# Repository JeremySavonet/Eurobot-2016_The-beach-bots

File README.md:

EUROBOT 2016 - The Beach Bots
====

TODO <br><br>

<h4>HW description:</h4>
----

Board : https://www.olimex.com/Products/ARM/ST/STM32-E407/open-source-hardware <br>
Motor Driver : https://www.olimex.com/Products/RobotParts/MotorDrivers/BB-VNH3SP30/open-source-hardware<br>
WiFi IoT module : https://www.olimex.com/Products/IoT/MOD-WIFI-ESP8266/open-source-hardware<br> 
=> Github : https://github.com/espressif/esp8266_at<br>

<h4>SW description:</h4>
----

Need to test those two RTOS:<br>

<li>Freertos : https://github.com/frtos-wpan/freertos-201309/tree/master/FreeRTOS/Demo/E407</li>
<li>ChibiOS : http://chibios.org/dokuwiki/doku.php?id=chibios:documentation:start</li>
    
Chibios seems to be a better alternative than FreeRtos for severals reasons:<br>
<li>maintaining our own hal eats a lot of development time - ChibiOS comes with a hal</li>
<li>pios hal is not being widely used and tested - ChibiOS is</li>
<li>FreeRTOS relies 100% on dynamic memory allocation (heap) - ChibiOS can do static as well as dynamic memory (even mixed)</li>
<li>FreeRTOS api is not type safe (mutex / semaphore / queue) - ChibiOS api is type safe</li>
<li>i have a feeling that ChibiOS is more efficient than FreeRTOS</li>
<li>using ChibiOS hal will make us stop relying on the buggy ST libraries in the longer term</li>

<h5>How to setup the env:</h5>

<li>Install arm gcc:</li>
<ul>brew tap PX4/homebrew-px4</ul>
<ul>brew update</ul>
<ul>brew install gcc-arm-none-eabi</ul>

<li>Install dfu-util:</li>
<ul>brew install dfu-util</ul>

<li>Make the projet:</li>
<ul>Just run make in the project folder</ul>

<li>Program the target:</li>
<ul>Put the device in dfu mode (set the jumper like explain in the manual</ul>
<ul>Run the command: dfu-util -v -d 0483:df11 -a 0 -s 0x08000000 -D prog.hex</ul>

<h4>Usefull links:</h4>
----

<li>https://www.alexwhittemore.com/using-the-stm32f4discovery-on-the-mac-os-x-10-8-4-command-line/</li>
<li>http://www.telecom-robotics.org/2013/08/robotics-101-quick-start/</li>

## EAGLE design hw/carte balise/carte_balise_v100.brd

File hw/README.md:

HW SECTION:
====

TODO:
----

<li> Add pull-up resistors </li>
<li> Update restrict zones </li>
<li> Update polygons clearance </li>

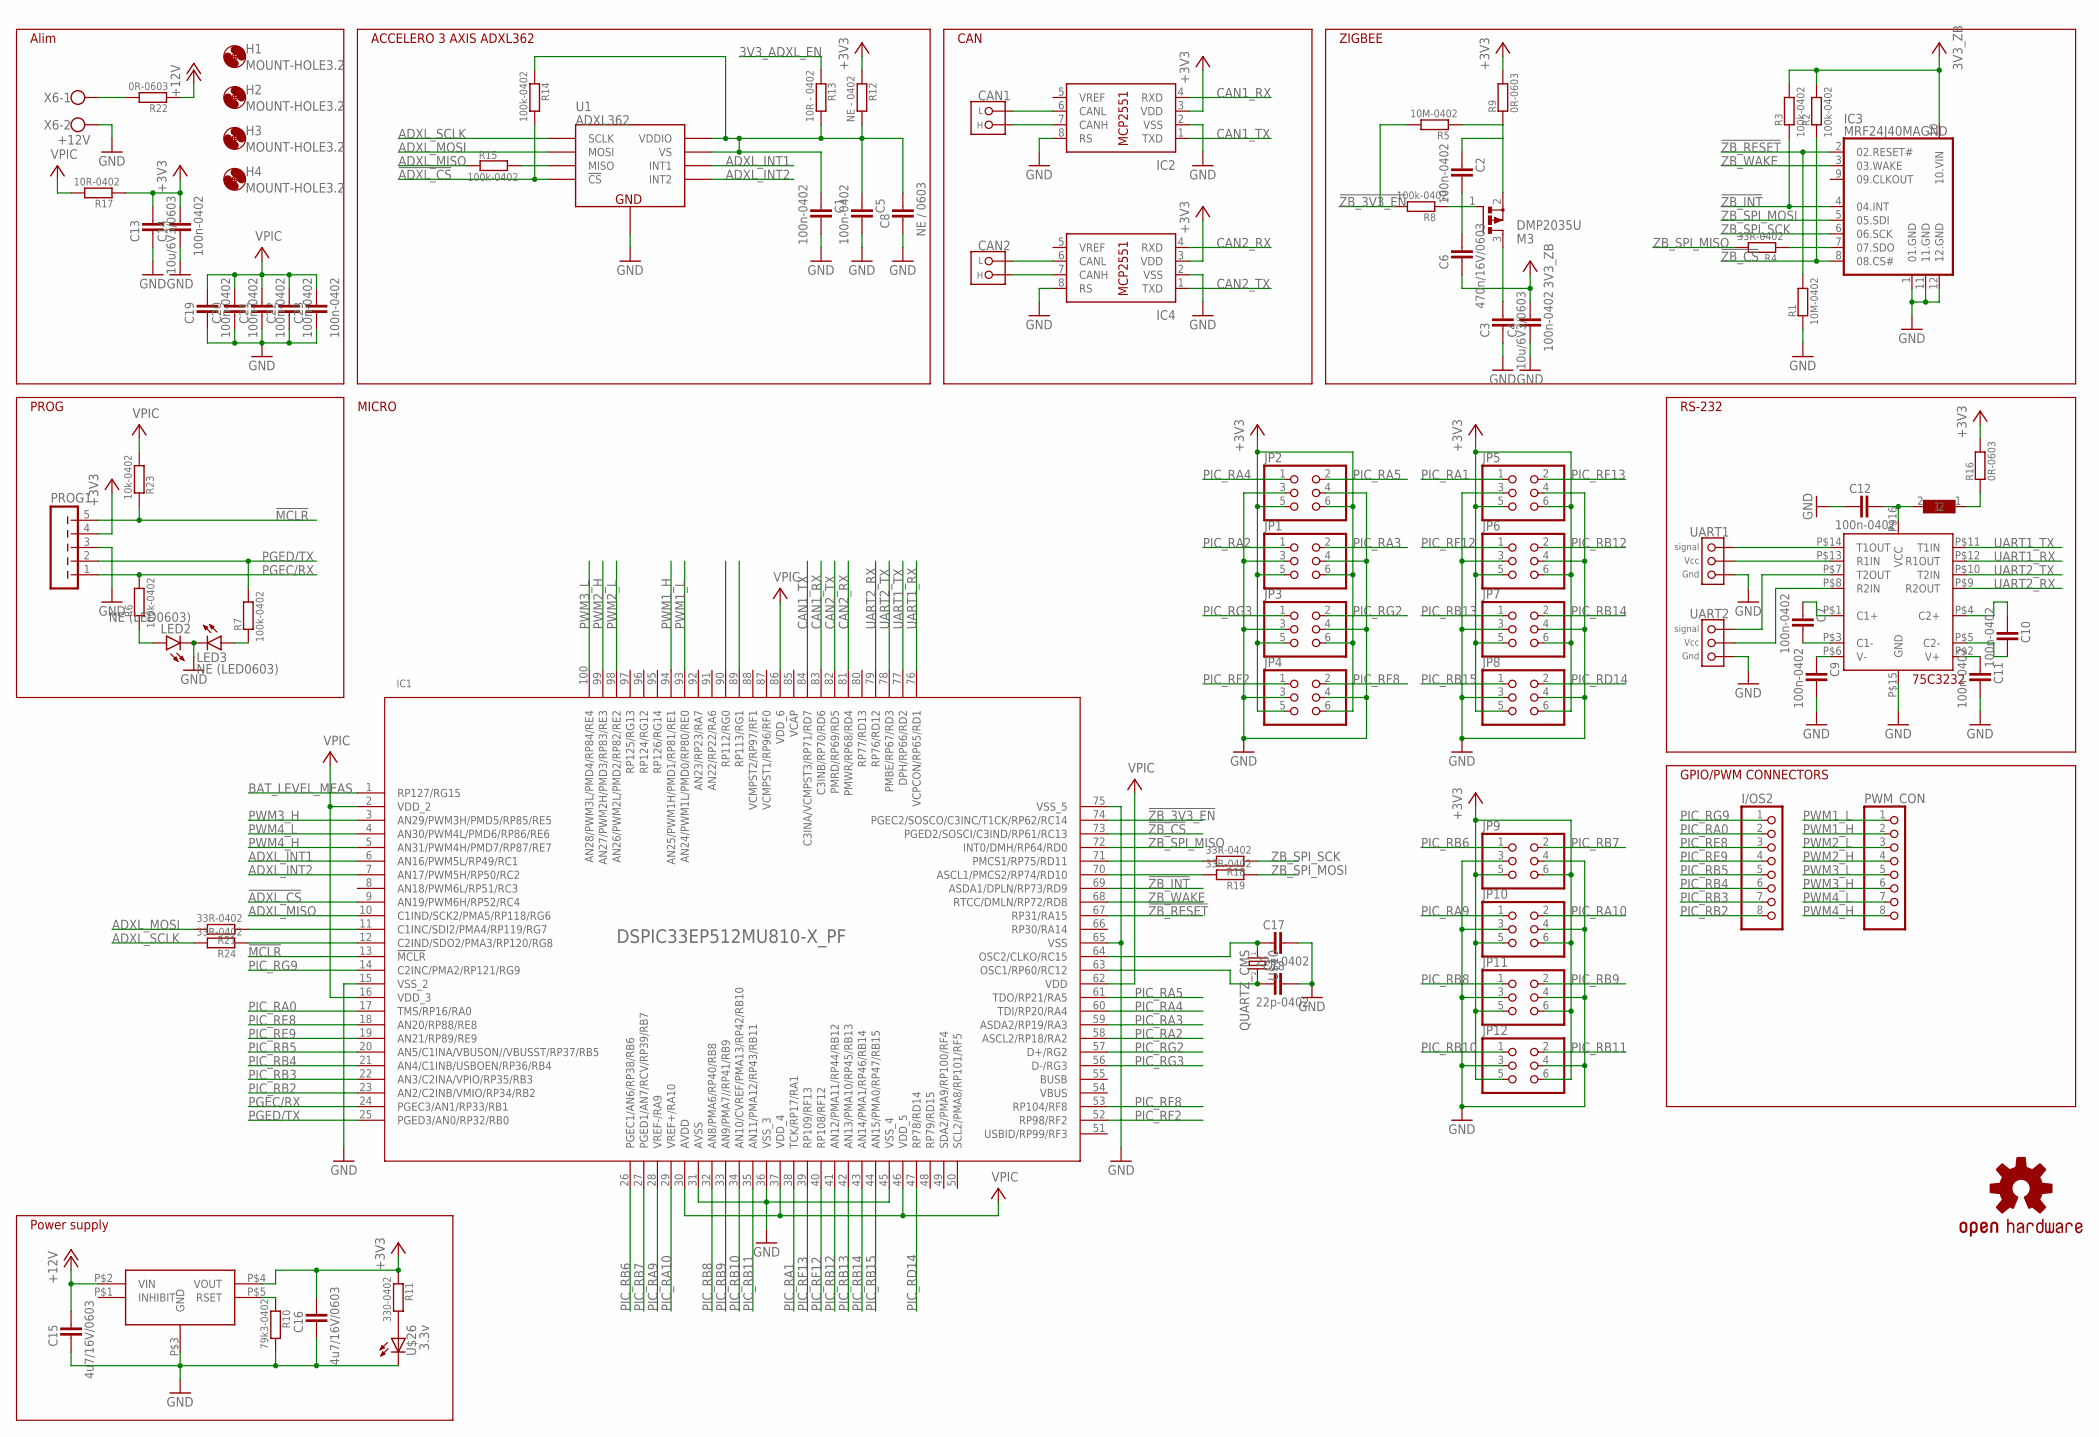
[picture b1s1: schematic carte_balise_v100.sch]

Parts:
C1, C2, C4, C5, C7, C9, C10, C11, C12, C14, C19, C20, C21, C22, C23: 100n-0402; 0402K
C3, C13: 10u/6V3/0603; 0603K
C6: 470n/16V/0603; 0603K
C8: NE / 0603; 0603K
C15, C16: 4u7/16V/0603; 0603K
C17, C18: 22p-0402; 0402K
CAN1, CAN2: CONNECT_CAN
H1, H2, H3, H4: MOUNT-HOLE3.2; 3,2
I/OS2: PINHD-1X08_2.54; 1X08
IC1: DSPIC33EP512MU810-X_PF; TQFP100_14X14MC
IC2, IC4: MCP2551/SN; SO08
IC3: MRF24J40MAGND; MRF24J40MA_2
JP1, JP2, JP3, JP4, JP5, JP6, JP7, JP8, JP9, JP10, JP11, JP12: PINHD-2X3; 2X03
LED2, LED3: NE (LED0603); 0603K
M3: DMP2035U; SOT23-3
PROG1: FE05-1
PWM_CON: PINHD-1X08_2.54; 1X08
R1, R5: 10M-0402; 0402K
R2, R3, R6, R7, R8, R14, R15: 100k-0402; 0402K
R4, R18, R19, R21, R24: 33R-0402; 0402K
R9, R16, R22: 0R-0603; 0603K
R10: 79k3-0402; 0402K
R11: 330-0402; 0402K
R12: NE - 0402; 0402K
R13: 10R - 0402; 0402K
R17: 10R-0402; 0402K
R23: 10k-0402; 0402K
U1: ADXL362
U$1: OSHW-LOGOS; OSHW-LOGO-S
U$2: SN75C3232_PW; PW16
U$3: L_603; 0603
U$10: QUARTZ_CMS
U$26: 3.3v; 805
U$27: PTR08100W
UART1, UART2: CONNECT_3PINS_CMS; CON_2.54_3
X6: +12V; W237-102

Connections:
3V3_ADXL_EN: R13.1
!ADXL_CS: IC1.9 (AN19/PWM6H/RP52/RC4), R14.2, U1.P$8 (!CS)
!MCLR: IC1.13 (!MCLR), PROG1.5, R23.1
!ZB_3V3_EN: IC1.74 (PGEC2/SOSCO/C3INC/T1CK/RP62/RC14), R5.2, R8.2
!ZB_CS: IC1.73 (PGED2/SOSCI/C3IND/RP61/RC13), IC3.8 (08.CS#), R2.1
!ZB_INT: IC1.69 (ASDA1/DPLN/RP73/RD9), IC3.4 (04.INT), R3.1
!ZB_RESET: IC1.67 (RP31/RA15), IC3.2 (02.RESET#), R1.2
+3V3: C13.1, C14.1, C16.1, IC2.3 (VDD), IC4.3 (VDD), JP1.5, JP1.6, JP2.5, JP2.6, JP3.5, JP3.6, JP4.5, JP4.6, JP5.5, JP5.6, JP6.5, JP6.6, JP7.5, JP7.6, JP8.5, JP8.6, JP9.5, JP9.6, JP10.5, JP10.6, JP11.5, JP11.6, JP12.5, JP12.6, PROG1.4, R9.2, R11.1, R12.1, R16.2, R17.1, U$27.P$4 (VOUT)
+12V: C15.1, R22.1, U$27.P$2 (VIN)
ADXL_INT1: IC1.6 (AN16/PWM5L/RP49/RC1), U1.P$11 (INT1)
ADXL_INT2: IC1.7 (AN17/PWM5H/RP50/RC2), U1.P$9 (INT2)
ADXL_MISO: IC1.10 (C1IND/SCK2/PMA5/RP118/RG6), R15.1
ADXL_MOSI: R21.2, U1.P$6 (MOSI)
ADXL_SCLK: R24.2, U1.P$4 (SCLK)
BAT_LEVEL_MEAS: IC1.1 (RP127/RG15)
BUSB: IC1.55 (BUSB)
CAN1_RX: IC1.83 (C3INB/RP70/RD6), IC2.4 (RXD)
CAN1_TX: IC1.84 (C3INA/VCMPST3/RP71/RD7), IC2.1 (TXD)
CAN2_RX: IC1.81 (PMWR/RP68/RD4), IC4.4 (RXD)
CAN2_TX: IC1.82 (PMRD/RP69/RD5), IC4.1 (TXD)
GND: C1.1, C3.2, C4.2, C5.1, C8.2, C9.1, C11.1, C12.2, C13.2, C14.2, C15.2, C16.2, C17.1, C18.1, C19.2, C20.2, C21.2, C22.2, C23.2, IC1.15 (VSS_2), IC1.31 (AVSS), IC1.36 (VSS_3), IC1.45 (VSS_4), IC1.65 (VSS), IC1.75 (VSS_5), IC2.2 (VSS), IC2.8 (RS), IC3.1 (01.GND), IC3.11 (11.GND), IC3.12 (12.GND), IC4.2 (VSS), IC4.8 (RS), JP1.3, JP1.4, JP2.3, JP2.4, JP3.3, JP3.4, JP4.3, JP4.4, JP5.3, JP5.4, JP6.3, JP6.4, JP7.3, JP7.4, JP8.3, JP8.4, JP9.3, JP9.4, JP10.3, JP10.4, JP11.3, JP11.4, JP12.3, JP12.4, LED2.K (C), LED3.K (C), PROG1.3, R1.1, R10.2, U1.P$12 (GND), U1.P$13 (GND), U1.P$16 (GND), U$2.P$15 (GND), U$26.2 (K), U$27.P$3 (GND), UART1.P$1 (_GND), UART2.P$1 (_GND), X6.2
unnamed: C2.1, C6.1, M3.1 (G), R8.1
unnamed: C2.2, M3.2 (S), R5.1, R9.1
unnamed: U$2.P$14 (T1OUT), UART1.P$3 (_SIGN)
unnamed: C1.2, C5.2, C8.1, R12.2, R13.2, R14.1, U1.P$1 (VDDIO), U1.P$14 (VS)
unnamed: R15.2, U1.P$7 (MISO)
unnamed: U$2.P$13 (R1IN), UART1.P$2 (_VCC)
unnamed: IC3.7 (07.SDO), R4.1
unnamed: CAN2._L, IC4.6 (CANL)
unnamed: C7.2, U$2.P$1 (C1+)
unnamed: IC1.12 (C2IND/SDO2/PMA3/RP120/RG8), R24.1
unnamed: LED2.A, R6.1
unnamed: C9.2, U$2.P$6 (V-)
unnamed: LED3.A, R7.1
unnamed: C7.1, U$2.P$3 (C1-)
unnamed: C11.2, U$2.P$2 (V+)
unnamed: C10.1, U$2.P$5 (C2-)
unnamed: C10.2, U$2.P$4 (C2+)
unnamed: C12.1, U$2.P$16 (VCC), U$3.2
unnamed: R16.1, U$3.1
unnamed: CAN1._L, IC2.6 (CANL)
unnamed: CAN1._H, IC2.7 (CANH)
unnamed: CAN2._H, IC4.7 (CANH)
unnamed: R11.2, U$26.1 (A)
unnamed: IC1.71 (PMCS1/RP75/RD11), R18.2
unnamed: U$2.P$7 (T2OUT), UART2.P$3 (_SIGN)
unnamed: U$2.P$8 (R2IN), UART2.P$2 (_VCC)
unnamed: C18.2, IC1.63 (OSC1/RP60/RC12), U$10.P$2 (2)
unnamed: C17.2, IC1.64 (OSC2/CLKO/RC15), U$10.P$1 (1)
unnamed: R22.2, X6.1
unnamed: IC1.11 (C1INC/SDI2/PMA4/RP119/RG7), R21.1
unnamed: IC1.70 (ASCL1/PMCS2/RP74/RD10), R19.2
unnamed: R10.1, U$27.P$5 (RSET)
PGEC/RX: IC1.24 (PGEC3/AN1/RP33/RB1), PROG1.1, R6.2
PGED/TX: IC1.25 (PGED3/AN0/RP32/RB0), PROG1.2, R7.2
PIC_RA0: I/OS2.2, IC1.17 (TMS/RP16/RA0)
PIC_RA1: IC1.38 (TCK/RP17/RA1), JP5.1
PIC_RA2: IC1.58 (ASCL2/RP18/RA2), JP1.1
PIC_RA3: IC1.59 (ASDA2/RP19/RA3), JP1.2
PIC_RA4: IC1.60 (TDI/RP20/RA4), JP2.1
PIC_RA5: IC1.61 (TDO/RP21/RA5), JP2.2
PIC_RA9: IC1.28 (VREF-/RA9), JP10.1
PIC_RA10: IC1.29 (VREF+/RA10), JP10.2
PIC_RB2: I/OS2.8, IC1.23 (AN2/C2INB/VMIO/RP34/RB2)
PIC_RB3: I/OS2.7, IC1.22 (AN3/C2INA/VPIO/RP35/RB3)
PIC_RB4: I/OS2.6, IC1.21 (AN4/C1INB/USBOEN/RP36/RB4)
PIC_RB5: I/OS2.5, IC1.20 (AN5/C1INA/VBUSON//VBUSST/RP37/RB5)
PIC_RB6: IC1.26 (PGEC1/AN6/RP38/RB6), JP9.1
PIC_RB7: IC1.27 (PGED1/AN7/RCV/RP39/RB7), JP9.2
PIC_RB8: IC1.32 (AN8/PMA6/RP40/RB8), JP11.1
PIC_RB9: IC1.33 (AN9/PMA7//RP41/RB9), JP11.2
PIC_RB10: IC1.34 (AN10/CVREF/PMA13/RP42/RB10), JP12.1
PIC_RB11: IC1.35 (AN11/PMA12/RP43/RB11), JP12.2
PIC_RB12: IC1.41 (AN12/PMA11/RP44/RB12), JP6.2
PIC_RB13: IC1.42 (AN13/PMA10/RP45/RB13), JP7.1
PIC_RB14: IC1.43 (AN14/PMA1/RP46/RB14), JP7.2
PIC_RB15: IC1.44 (AN15/PMA0/RP47/RB15), JP8.1
PIC_RD14: IC1.47 (RP78/RD14), JP8.2
PIC_RE8: I/OS2.3, IC1.18 (AN20/RP88/RE8)
PIC_RE9: I/OS2.4, IC1.19 (AN21/RP89/RE9)
PIC_RF2: IC1.52 (RP98/RF2), JP4.1
PIC_RF8: IC1.53 (RP104/RF8), JP4.2
PIC_RF12: IC1.40 (RP108/RF12), JP6.1
PIC_RF13: IC1.39 (RP109/RF13), JP5.2
PIC_RG2: IC1.57 (D+/RG2), JP3.2
PIC_RG3: IC1.56 (D-/RG3), JP3.1
PIC_RG9: I/OS2.1, IC1.14 (C2INC/PMA2/RP121/RG9)
PWM1_H: IC1.94 (AN25/PWM1H/PMD1/RP81/RE1), PWM_CON.2
PWM1_L: IC1.93 (AN24/PWM1L/PMD0/RP80/RE0), PWM_CON.1
PWM2_H: IC1.99 (AN27/PWM2H/PMD3/RP83/RE3), PWM_CON.4
PWM2_L: IC1.98 (AN26/PWM2L/PMD2/RP82/RE2), PWM_CON.3
PWM3_H: IC1.3 (AN29/PWM3H/PMD5/RP85/RE5), PWM_CON.6
PWM3_L: IC1.100 (AN28/PWM3L/PMD4/RP84/RE4), PWM_CON.5
PWM4_H: IC1.5 (AN31/PWM4H/PMD7/RP87/RE7), PWM_CON.8
PWM4_L: IC1.4 (AN30/PWM4L/PMD6/RP86/RE6), PWM_CON.7
UART1_RX: IC1.76 (VCPCON/RP65/RD1), U$2.P$12 (R1OUT)
UART1_TX: IC1.77 (DPH/RP66/RD2), U$2.P$11 (T1IN)
UART2_RX: IC1.79 (RP76/RD12), U$2.P$9 (R2OUT)
UART2_TX: IC1.78 (PMBE/RP67/RD3), U$2.P$10 (T2IN)
V+: C19.1, C20.1, C21.1, C22.1, C23.1, IC1.2 (VDD_2), IC1.16 (VDD_3), IC1.30 (AVDD), IC1.37 (VDD_4), IC1.46 (VDD_5), IC1.62 (VDD), IC1.86 (VDD_6), R17.2
VBUS: IC1.54 (VBUS)
VCAP: IC1.85 (VCAP)
VDD_RADIO: C3.1, C4.1, C6.2, IC3.10 (10.VIN), M3.3 (D), R2.2, R3.2
VPIC: R23.2
ZB_SPI_MISO: IC1.72 (INT0/DMH/RP64/RD0), R4.2
ZB_SPI_MOSI: IC3.5 (05.SDI), R19.1
ZB_SPI_SCK: IC3.6 (06.SCK), R18.1
ZB_WAKE: IC1.68 (RTCC/DMLN/RP72/RD8), IC3.3 (03.WAKE)

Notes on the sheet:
MICRO
ZIGBEE
Alim
ACCELERO 3 AXIS ADXL362
RS-232
CAN
Power supply
GPIO/PWM CONNECTORS
PROG

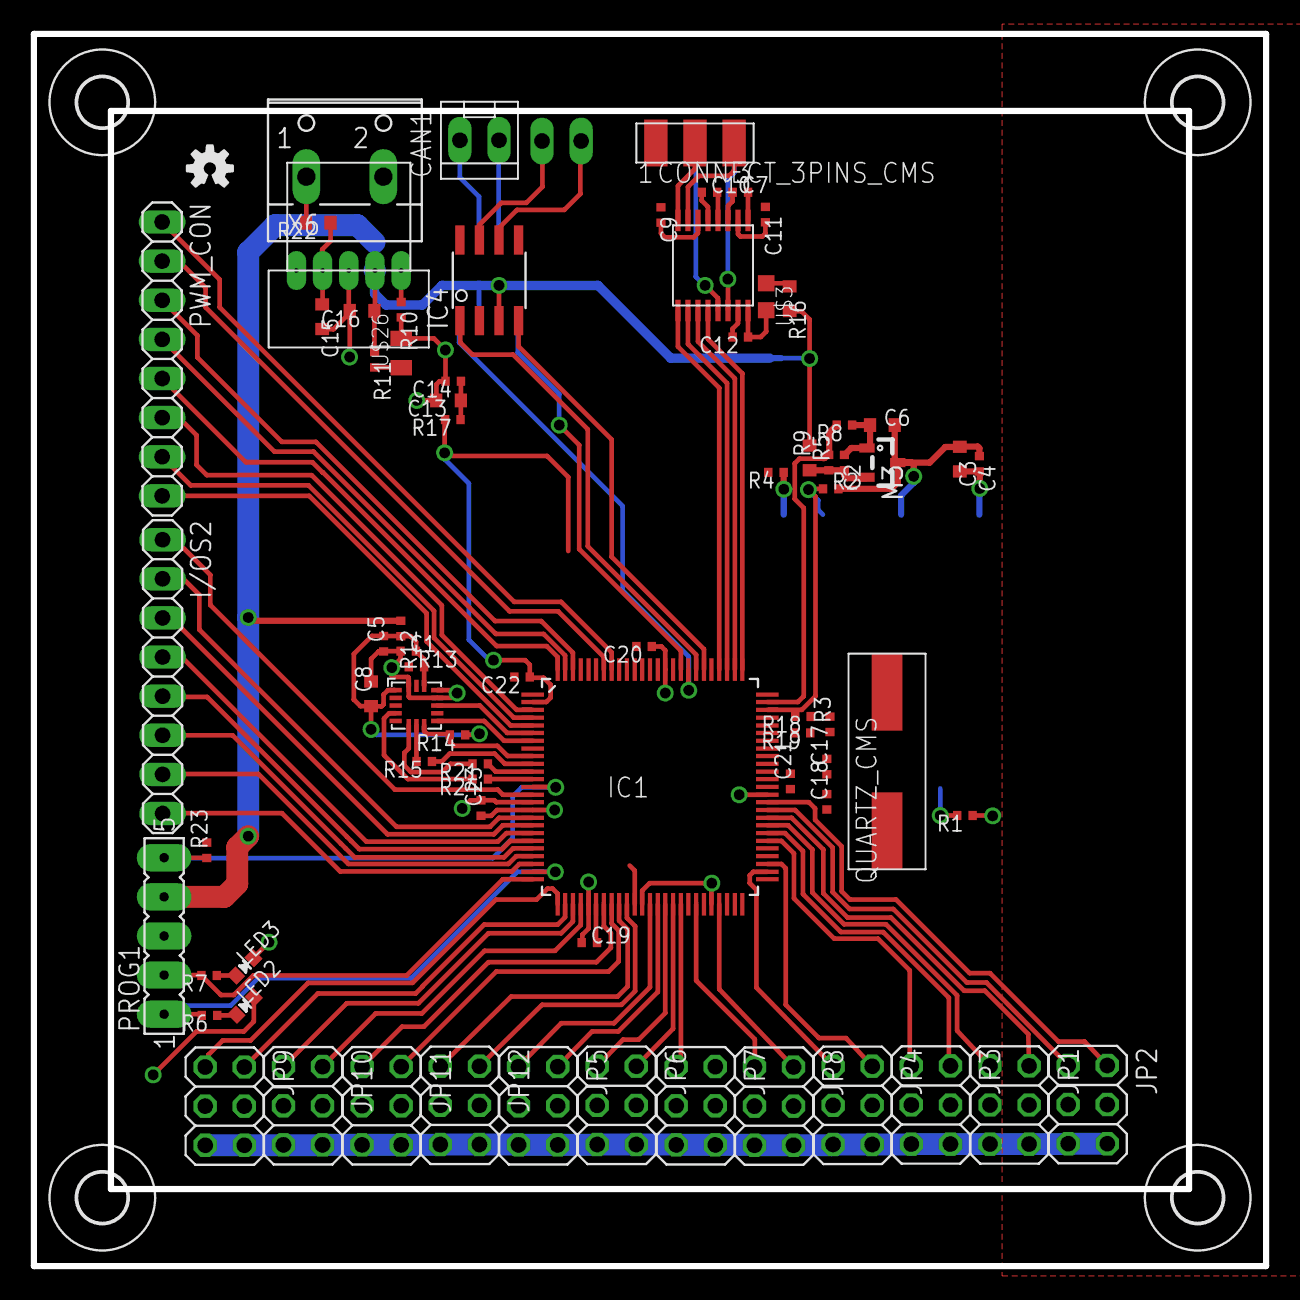
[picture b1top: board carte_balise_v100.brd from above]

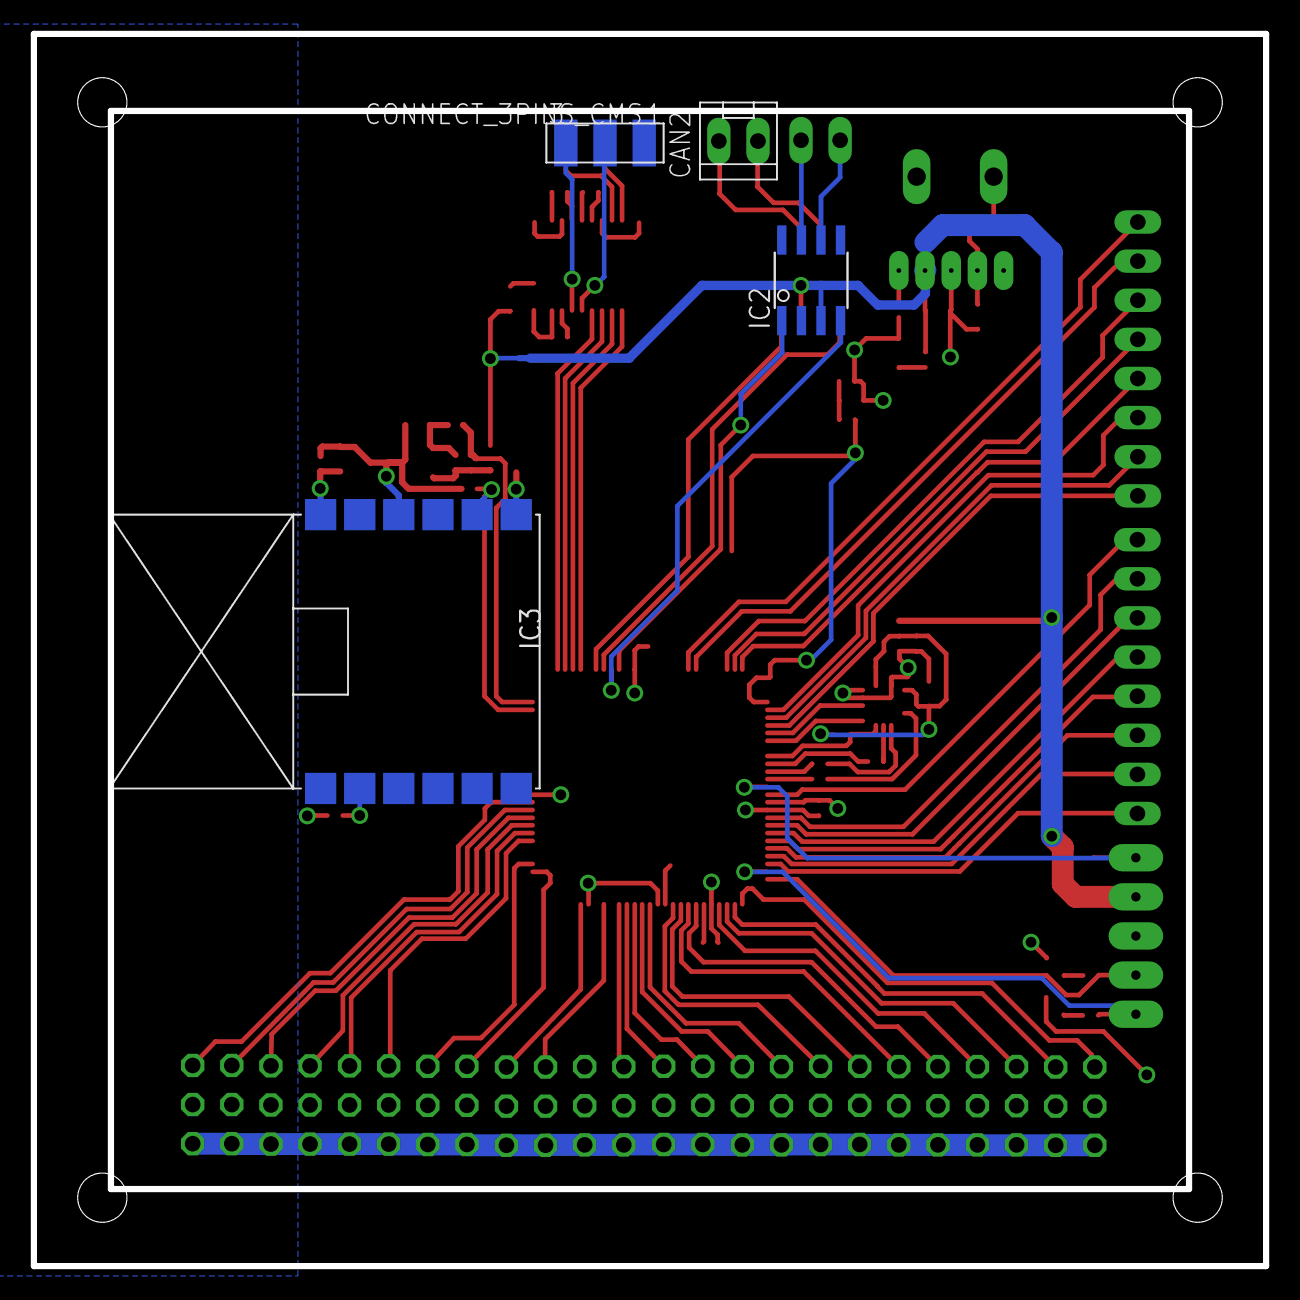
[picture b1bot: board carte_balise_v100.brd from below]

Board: 2 copper layers, 80.0 x 80.0 mm, 84 parts (4 on the bottom side), 102 nets.

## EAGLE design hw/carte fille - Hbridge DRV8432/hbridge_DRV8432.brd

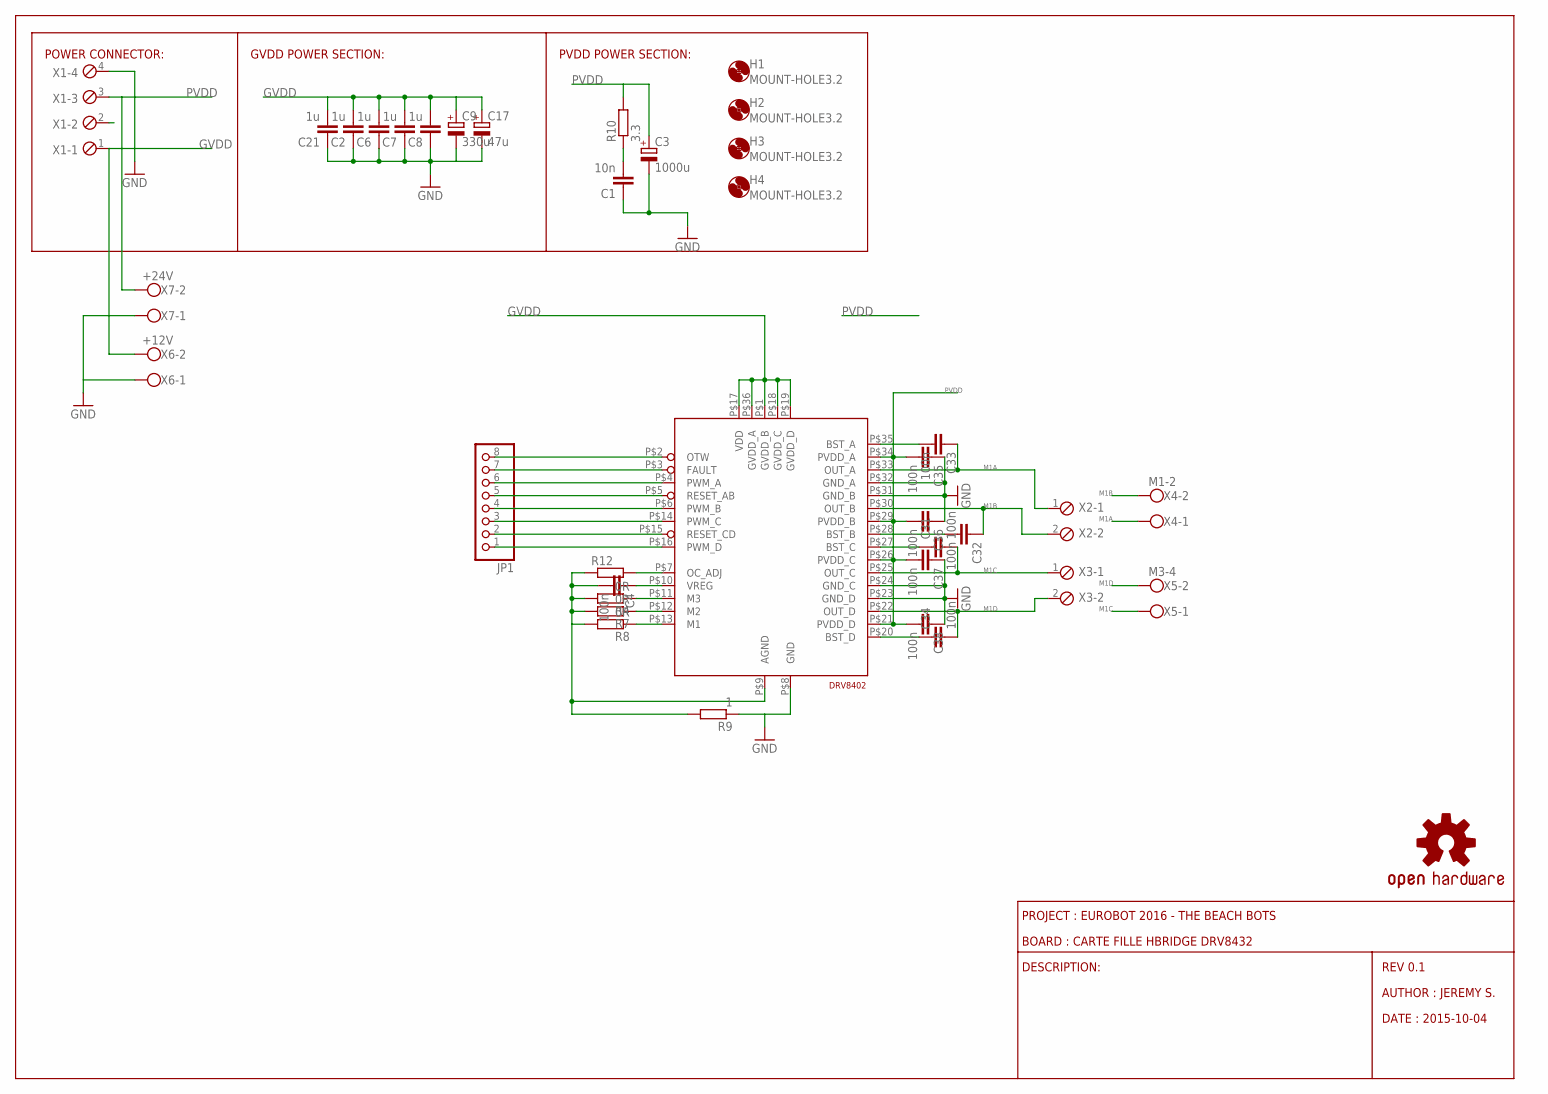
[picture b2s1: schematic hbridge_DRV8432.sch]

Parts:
C1: 10n; C0805
C2, C6, C7, C8, C21: 1u; C0805
C3: 1000u; E3,5-10
C4: 100n; C0603K
C9: 330u; B/3528-21W
C17: 47u; B/3528-21W
C31, C32, C33, C34: 100n; C0805
C35, C36, C37, C38: 100n; C0603
H1, H2, H3, H4: MOUNT-HOLE3.2; 3,2
IC1: DRV8402
JP1: PINHD-1X08_2.54; 1X08
R4, R7, R8: 0R; R0603
R9: 1; R0603
R10: 3.3; R1206
R12: R-EU_R0603; R0603
U$1: OSHW-LOGOS; OSHW-LOGO-S
X1: MPT4; 4POL254
X2, X3: MPT2; 2POL254
X4: M1-2; W237-102
X5: M3-4; W237-102
X6: +12V; W237-102
X7: +24V; W237-102

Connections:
GND: C1.1, C2.1, C3.-, C6.1, C7.1, C8.1, C9.-, C17.-, C21.1, C35.1, C36.1, C37.1, C38.1, IC1.P$8 (GND), IC1.P$23 (GND_D), IC1.P$24 (GND_C), IC1.P$31 (GND_B), IC1.P$32 (GND_A), R9.1, X1.4, X6.1, X7.1
GVDD: C2.2, C6.2, C7.2, C8.2, C9.+, C17.+, C21.2, IC1.P$1 (GVDD_B), IC1.P$17 (VDD), IC1.P$18 (GVDD_C), IC1.P$19 (GVDD_D), IC1.P$36 (GVDD_A), X1.1, X6.2
M1A: C33.1, IC1.P$33 (OUT_A), X2.1, X4.1
M1B: C32.1, IC1.P$30 (OUT_B), X2.2, X4.2
M1C: C31.2, IC1.P$25 (OUT_C), X3.1, X5.1
M1D: C34.2, IC1.P$22 (OUT_D), X3.2, X5.2
unnamed: IC1.P$2 (OTW), JP1.8
unnamed: IC1.P$13 (M1), R8.1
unnamed: IC1.P$12 (M2), R7.1
unnamed: IC1.P$11 (M3), R4.1
unnamed: IC1.P$3 (FAULT), JP1.7
unnamed: IC1.P$4 (PWM_A), JP1.6
unnamed: C4.2, IC1.P$9 (AGND), R4.2, R7.2, R8.2, R9.2, R12.1
unnamed: IC1.P$7 (OC_ADJ), R12.2
unnamed: C4.1, IC1.P$10 (VREG)
unnamed: C1.2, R10.1
unnamed: IC1.P$5 (RESET_AB), JP1.5
unnamed: IC1.P$6 (PWM_B), JP1.4
unnamed: IC1.P$14 (PWM_C), JP1.3
unnamed: IC1.P$15 (RESET_CD), JP1.2
unnamed: IC1.P$16 (PWM_D), JP1.1
unnamed: C33.2, IC1.P$35 (BST_A)
unnamed: C32.2, IC1.P$28 (BST_B)
unnamed: C31.1, IC1.P$27 (BST_C)
unnamed: C34.1, IC1.P$20 (BST_D)
PVDD: C3.+, C35.2, C36.2, C37.2, C38.2, IC1.P$21 (PVDD_D), IC1.P$26 (PVDD_C), IC1.P$29 (PVDD_B), IC1.P$34 (PVDD_A), R10.2, X1.3, X7.2

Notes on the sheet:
REV 0.1
AUTHOR : JEREMY S.
DATE : 2015-10-04
DESCRIPTION:
PROJECT : EUROBOT 2016 - THE BEACH BOTS
BOARD : CARTE FILLE HBRIDGE DRV8432
GVDD POWER SECTION:
POWER CONNECTOR:
PVDD POWER SECTION:

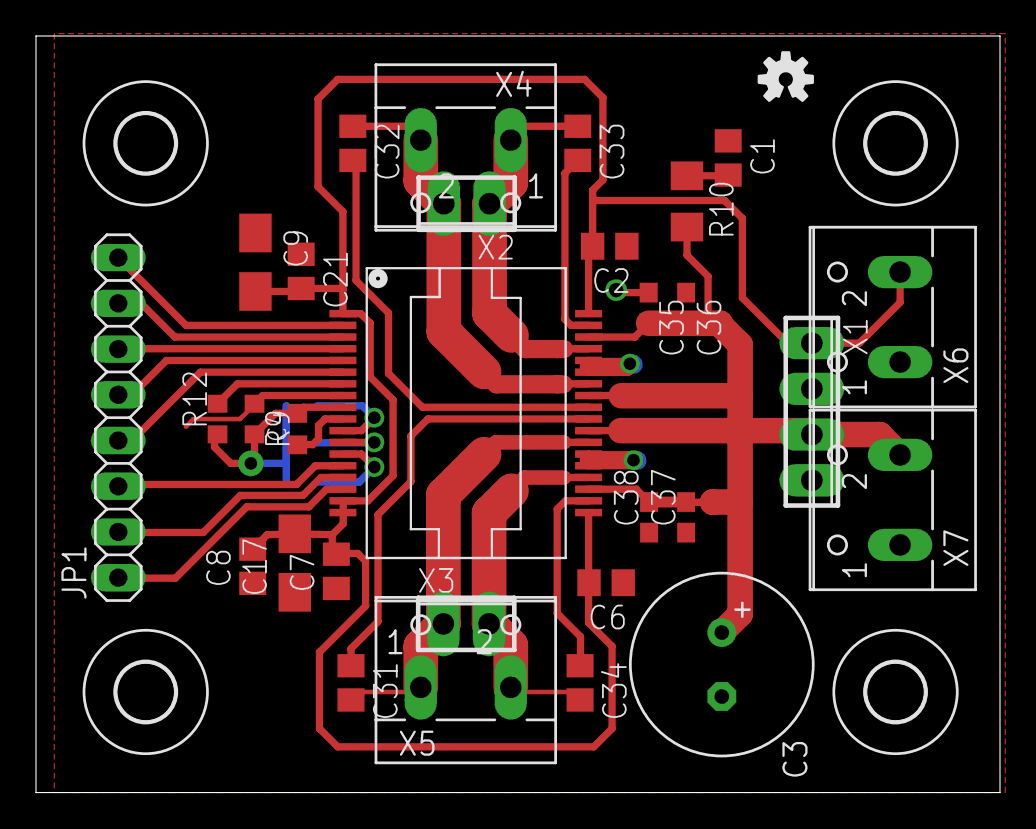
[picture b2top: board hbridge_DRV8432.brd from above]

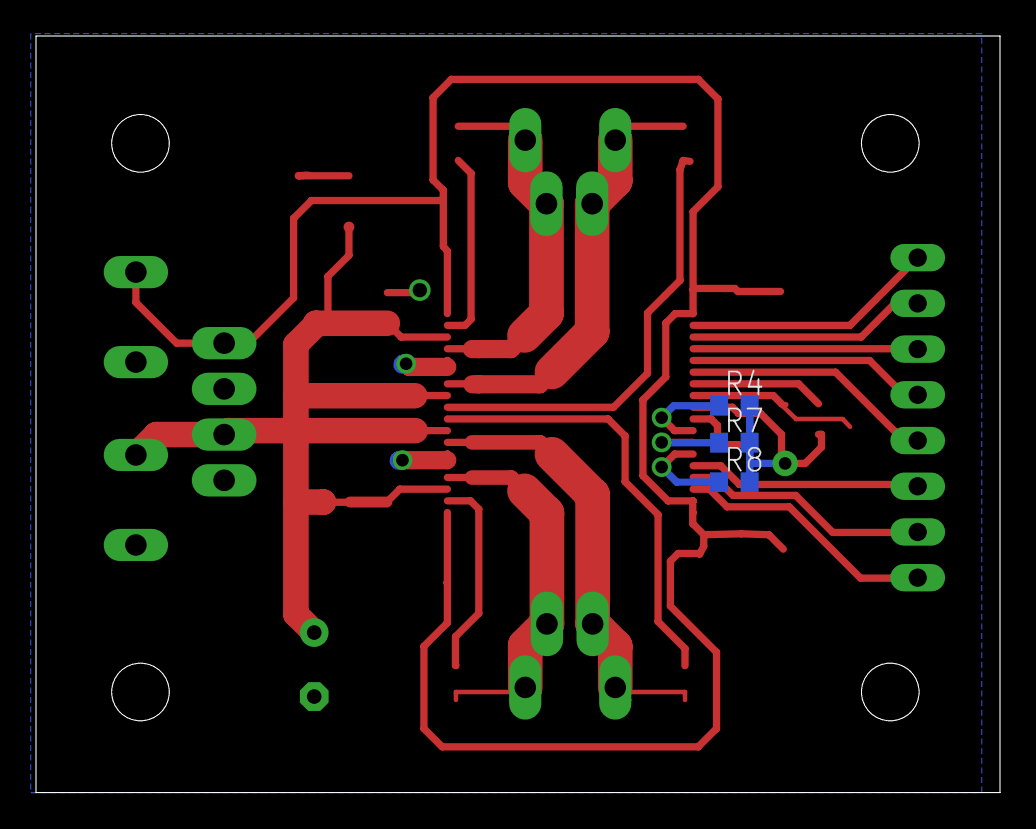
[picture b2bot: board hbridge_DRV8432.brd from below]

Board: 2 copper layers, 53.6 x 42.0 mm, 38 parts (3 on the bottom side), 26 nets.

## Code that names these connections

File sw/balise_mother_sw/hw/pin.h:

#ifndef _PIN_H
#define	_PIN_H

#include "system.h"

// Adxl 362
#define ADXL_INT1                   _RB12
#define ADXL_INT2                   _RB13
#define ADXL_CSn                    _LATB14
#define ADXL_3V3_EN                 _LATE5

// Leds
#define LED1                        _LATE4
#define LED3                        _LATE6
#define LED4                        _LATE7

// Version board
#define VER_B0                      _RE0        //LSB
#define VER_B1                      _RE1
#define VER_B2                      _RE2
#define VER_B3                      _RE3        //MSB
#define PCB_VER                     (PORTE & 0xf)

#define BAT                         11

#endif //_PIN_H

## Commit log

2015-10-03 Add eurobot 2016 rules
2015-10-03 Add dev board datasheet and manual
2015-10-03 Add some datasheets
2015-10-03 update gitignore and rm unused file
2015-10-03 Add IoT WiFi specifications
2015-10-03 Add ChibiOS and simple demo program
2015-10-03 Update gitignore
2015-10-04 HBridge board WIP
2015-10-04 Cleanup ChibiOS folder
2015-10-04 Add readme file in hw folder
2015-10-04 Fix issue with lwip and fatfs Update HelloWolrd project
2015-10-04 Start routing the board
2015-10-04 Update Readme file in hw section
2015-10-10 rework board routing
2015-10-10 finish routing
2015-10-11 fix power section
2015-10-11 add openOCD tool (mac build)
2015-10-11 add openOCD config files for differents platform
2015-10-11 template project for balise
2015-10-11 fix coding style
2015-10-11 add datasheets related to balise project
2015-10-18 start balise mother board
2015-10-18 add open hardware logo
2015-10-18 add dspic33E datasheet
2015-10-18 rework io connector and start routing the board
2015-10-19 add eagle sw
2015-10-24 add prog script
2015-10-24 minor change to make it works
2015-10-24 add uart module on usart3
2015-10-24 adding gameloop and stop all the thread after 90s
2015-10-24 rework the way we finish thread processing
2015-10-24 adding uext thread reader for modwifi
2015-10-25 project cleanup + fix ESP8266
2015-10-25 add pwm support on port D with TIM4
2015-10-25 start ESP8266 API
2015-10-25 add support for CLI on USB2 OTG
2015-10-25 remove extra delays
2015-10-26 start clean up cli over usb
2015-10-26 wip cleanup
2015-10-31 wip routing and placement
2015-11-01 WIP adxl
2015-11-02 wip board
2015-11-07 remove eagle sw
2015-11-07 start meca 2016
2015-11-07 remork shell to use microrl
2015-11-08 little cleanup and add shell color
2015-11-08 rework debug print and add some cool stuff on boot sequence
2015-11-08 fix ascii art
2015-11-08 start adc manager and cli module
2015-11-08 project cleanup
2015-11-08 cleanup wip
2015-11-08 fix last commit
2015-11-09 add altium balise project
2015-11-14 project cleanup and rework folder architecture
2015-11-14 start working on control system
2015-11-14 wip on control system -> adding some filters
2015-11-14 remove project balise
2015-11-14 format
2015-11-14 add position manager and common directory
2015-11-14 cs and format
2015-11-15 add blocking detection manager
2015-11-15 wip common module -> add geometry submodules for trajectory manager
2015-11-15 cleanup includes
2015-11-15 start format geometry module
2015-11-15 clean trajectory manager
2015-11-15 add obstacle avoidance and trajectory manager modules
2015-11-15 rework debug print in new modules
2015-11-15 cleanup trajectory manager
2015-11-15 add core and utils in trajectory manager module
2015-11-15 add versatile constrol system module -> init odo/cs and define robot structure
2015-11-15 cleanup
2015-11-16 first attempt to pwm function pointer
2015-11-17 add QEI management in chibios
2015-11-17 minor fix in qei module integration
2015-11-17 fix qei module
2015-11-18 add debug to test pwm
2015-11-20 minor changes on pwm
2015-11-20 remap qei to TIM3/4 and PWM to TIM9. [ tested: ok]
2015-11-21 swtich to ChibiOS V3.0.3
2015-11-21 add ChibiOS 3.0.3 with STM32 QEI integration
2015-11-21 add ir sensor module and htpp server integration
2015-11-21 add readme file
2015-11-21 norme
2015-11-21 fix name
2015-11-21 fix command to return when wrong number of args
2015-11-21 clean motor_manager modules and add usefull commands to the CLI
2015-11-22 start working with global struct sys and add commands module
2015-11-22 rework infrared module. Add versatile_sensors manager. Update commands file
2015-11-22 add temperature sensor module
2015-11-22 add battery manager module
2015-11-22 factorize mode commands and move alive task in system file
2015-11-22 add usefull commands to CLI
2015-11-22 add strat management and update related commands in CLI
2015-11-22 add uptime commands in seconds
2015-11-23 add commands to set/get pid gains
2015-11-28 fix double start issue and stop issue
2015-11-28 start working on mrf24j40 zigbee module and beacon module
2015-11-28 remove unused global var in mrf24j40 module
2015-11-28 work on strat. Add scheduler and utils functions
2015-11-29 rework strat management
2016-05-10 partial cleanup and cs
2016-05-11 Add main board project
2016-05-11 Update helloworld project
2016-05-11 update HelloWorld readme file
2016-05-11 update mainboard readme file
2016-05-13 fix USB modem CLI on HelloWorld Project
2016-05-13 move esp8266 module in specific folder module
2016-05-13 move zigbee module in specific module folder
2016-05-13 move motor module in right subfolder
2016-05-13 Change PWM value to match our ESC
2016-05-14 Add chibios 3.0.5
2016-05-14 Add ChibiOS 16.1.4
2016-05-14 HelloWorld project move to ChibiOS 3.0.5
2016-05-14 MainBoard project move to ChibiOS 3.0.5
2016-05-14 Patch to support QEI driver for STM32F4XX platform (ChibiOS3.0.5)
2016-05-14 Rework microshell in HelloWorld project
2016-05-14 Rework microshell in MainBoard project
2016-05-14 Moving to Chibios 16.1.4 (HelloWorld)
2016-05-14 Moving to ChibiOS 16.1.4 (MainBoard)
2016-05-14 Rework microshell start_shell function
2016-05-14 Patch to support QEI driver for STM32F4XX platform (ChibiOS 16.1.4)
2016-05-14 Base structure for nucleo mems bring up
2016-05-17 Add cli boot message
2016-05-22 add fatfs support
2016-05-22 fix fatfs cat command
2016-05-22 rename properly dc module manager and split qei manager in separate module
2016-05-22 add brushless motor support
2016-05-22 update mainboard read with todo list
2016-05-22 fix in brushless motor module
2016-05-22 udpate todo list
2016-05-22 rework sys state and add can support
2016-10-09 repo cleanup

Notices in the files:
parts and their libraries:
SparkFun-Aesthetics: Licensing: CC v3.0 Share-Alike You are welcome to use this library for commercial purposes.
